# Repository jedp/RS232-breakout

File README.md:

# RS-232 breakout board

Based on MAX3232 line driver and receiver.

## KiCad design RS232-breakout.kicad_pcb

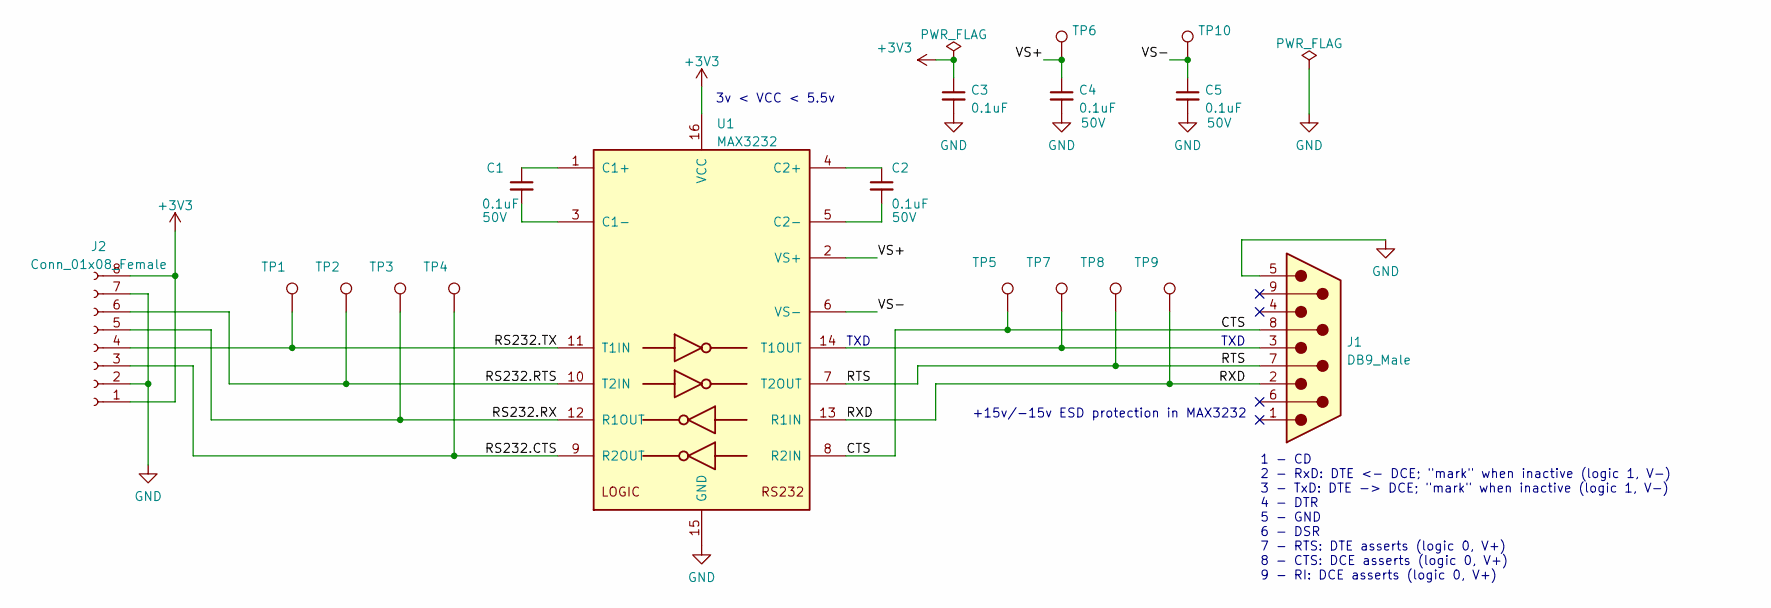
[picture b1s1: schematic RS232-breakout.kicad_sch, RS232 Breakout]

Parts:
C1, C2, C4, C5: 0.1uF; C_0603_1608Metric; Rating 50V
C3: 0.1uF; C_0603_1608Metric
J1: DB9_Male; AMPHENOL_LD09P13A4GV00LF
J2: Conn_01x08_Female; PinHeader_1x08_P2.54mm_Vertical
TP1, TP2, TP3, TP4, TP5, TP6, TP7, TP8, TP9, TP10: TestPoint; TestPoint_Pad_D1.0mm
U1: MAX3232; TSSOP-16_4.4x5mm_P0.65mm

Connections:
+3V3: C3.1, J2.1, J2.8, U1.16 (VCC)
/CTS: J1.8, TP5.1, U1.8 (R2IN)
/RS232.CTS: J2.3, TP4.1, U1.9 (R2OUT)
/RS232.RTS: J2.6, TP2.1, U1.10 (T2IN)
/RS232.RX: J2.5, TP3.1, U1.12 (R1OUT)
/RS232.TX: J2.4, TP1.1, U1.11 (T1IN)
/RTS: J1.7, TP8.1, U1.7 (T2OUT)
/RXD: J1.2, TP9.1, U1.13 (R1IN)
/VS+: C4.1, TP6.1, U1.2 (VS+)
/VS-: C5.1, TP10.1, U1.6 (VS-)
GND: C3.2, C4.2, C5.2, J1.5, J2.2, J2.7, U1.15 (GND)
unnamed: C1.1, U1.1 (C1+)
unnamed: C1.2, U1.3 (C1-)
unnamed: C2.1, U1.4 (C2+)
unnamed: C2.2, U1.5 (C2-)
unnamed: J1.3, TP7.1, U1.14 (T1OUT)

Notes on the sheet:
TXD
1 - CD 2 - RxD: DTE <- DCE; "mark" when inactive (logic 1, V-) 3 - TxD: DTE -> DCE; "mark" when inactive (logic 1, V-) 4 - DTR 5 - GND 6 - DSR 7 - RTS: DTE asserts (logic 0, V+) 8 - CTS: DCE asserts (logic 0, V+) 9 - RI: DCE asserts (logic 0, V+)
3v < VCC < 5.5v
+15v/-15v ESD protection in MAX3232

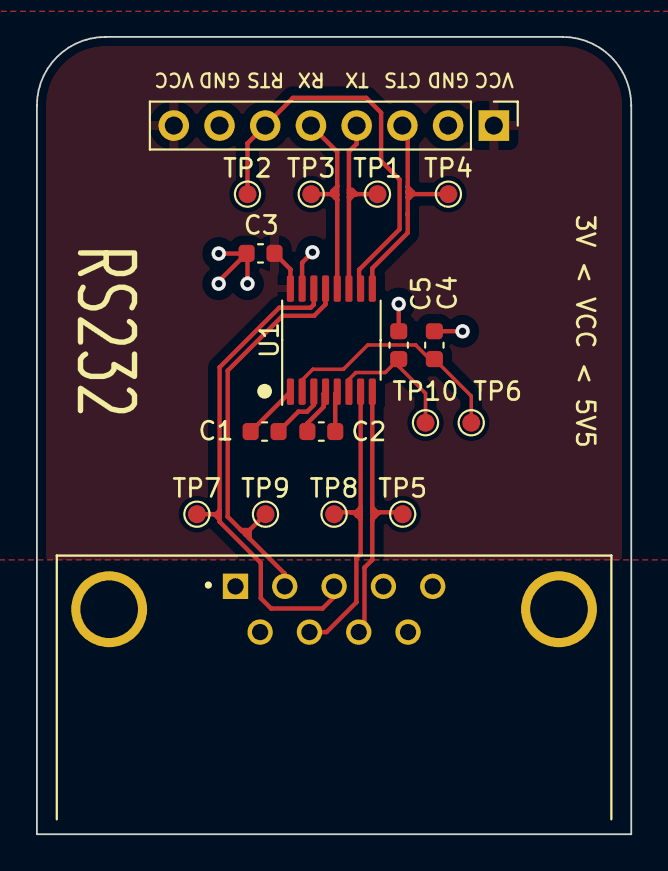
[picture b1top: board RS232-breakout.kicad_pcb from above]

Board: 2 copper layers, 33.0 x 44.3 mm, 18 parts (0 on the bottom side), 16 nets.

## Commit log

2023-12-26 RS232/MAX3232 breakout board
2023-12-26 PCB image
